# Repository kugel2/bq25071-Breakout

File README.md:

# bq25071-Breakout
Breakoutboard 20x20mm for bq25071 LiFePo4 linear charger ic.

**_Warning_: this board is not finished**

**_Warning_: this board is not tested**

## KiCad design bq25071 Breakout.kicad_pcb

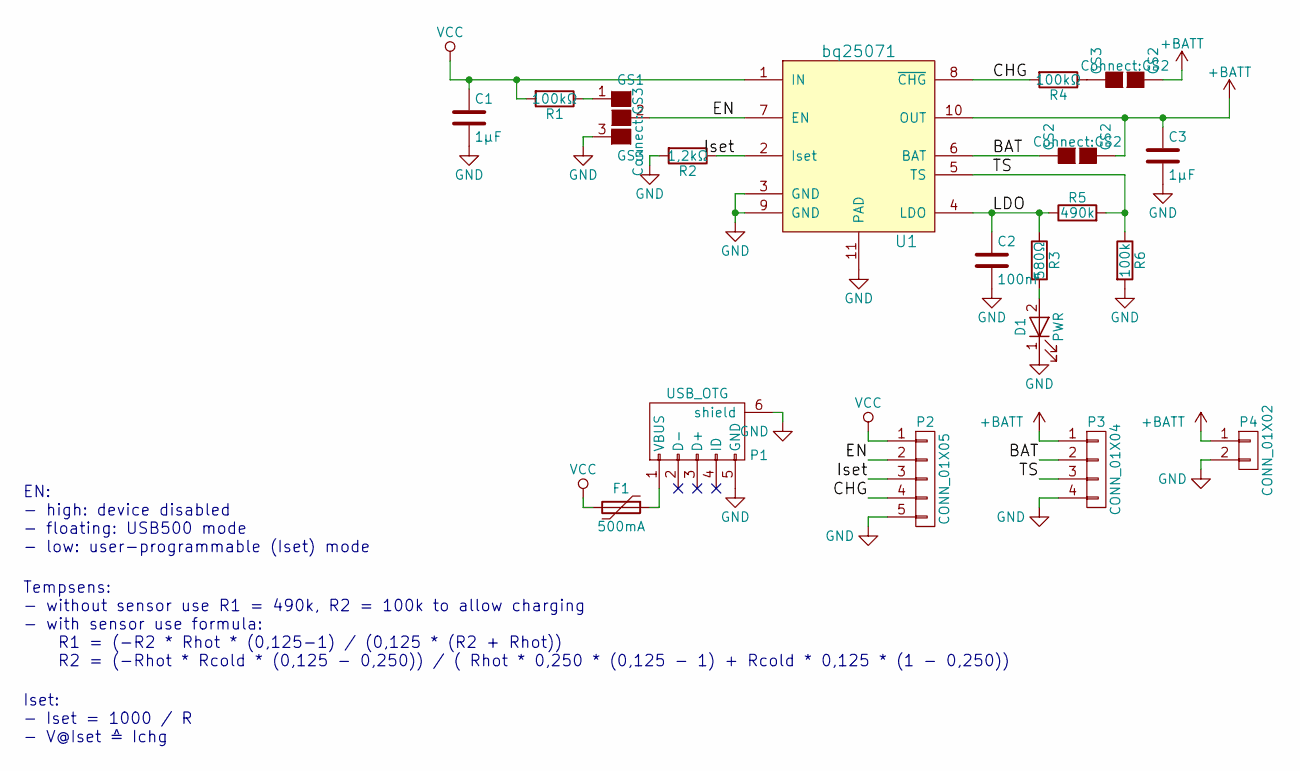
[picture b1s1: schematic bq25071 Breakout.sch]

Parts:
C1, C3: 1µF; C_1206
C2: 100nF; C_0805
D1: PWR; LED_0805
F1: 500mA; R_1206
GS1: GS3
GS2, GS3: GS2
P1: USB_OTG; USB_MICRO_B_MOLEX
P2: CONN_01X05; Pin_Header_Straight_1x05_Pitch2.54mm
P3: CONN_01X04; Pin_Header_Straight_1x04_Pitch2.54mm
P4: CONN_01X02; JST_XH_B02B-XH-A_02x2.50mm_Straight
R1, R4: 100kΩ; R_0805
R2: 1,2kΩ; R_0805
R3: 580Ω; R_0805
R5: 490k; R_0805
R6: 100k; R_0805
U1: bq25071; DFN-10-1EP_2x3mm_Pitch0.5mm

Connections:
+BATT: C3.1, GS2.2 (G2), GS3.2 (G2), P3.1, P4.1, U1.10 (OUT)
/BAT: GS2.1 (G1), P3.2, U1.6 (BAT)
/CHG: P2.4, R4.2, U1.8 (~CHG)
/EN: GS1.2 (G2), P2.2, U1.7 (EN)
/Iset: P2.3, R2.1, U1.2 (Iset)
/LDO: C2.1, R3.1, R5.1, U1.4 (LDO)
/TS: P3.3, R5.2, R6.1, U1.5 (TS)
GND: C1.2, C2.2, C3.2, D1.1 (K), GS1.3 (G3), P1.5 (GND), P1.6 (shield), P2.5, P3.4, P4.2, R2.2, R6.2, U1.3 (GND), U1.9 (GND), U1.11 (PAD)
unnamed: D1.2 (A), R3.2
unnamed: F1.1, P1.1 (VBUS)
unnamed: GS1.1 (G1), R1.1
unnamed: GS3.1 (G1), R4.1
VCC: C1.1, F1.2, P2.1, R1.2, U1.1 (IN)

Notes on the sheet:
Tempsens: - without sensor use R1 = 490k, R2 = 100k to allow charging - with sensor use formula: R1 = (-R2 * Rhot * (0,125-1) / (0,125 * (R2 + Rhot)) R2 = (-Rhot * Rcold * (0,125 - 0,250)) / ( Rhot * 0,250 * (0,125 - 1) + Rcold * 0,125 * (1 - 0,250))
EN: - high: device disabled - floating: USB500 mode - low: user-programmable (Iset) mode
Iset: - Iset = 1000 / R - V@Iset ≙ Ichg

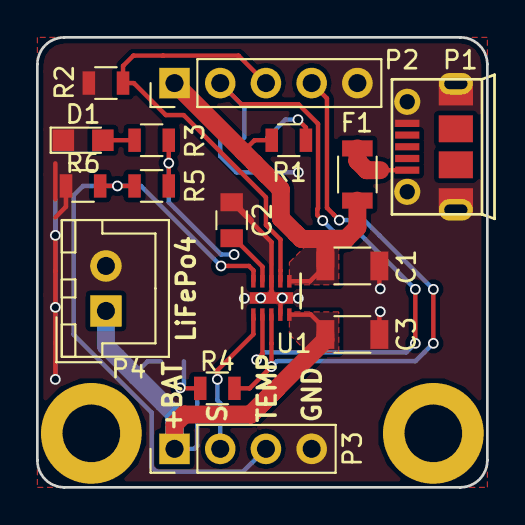
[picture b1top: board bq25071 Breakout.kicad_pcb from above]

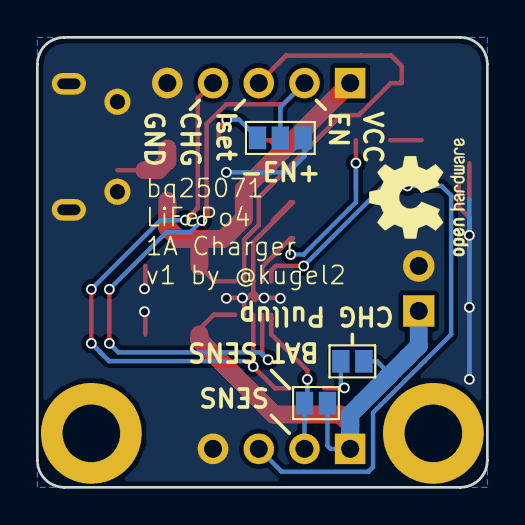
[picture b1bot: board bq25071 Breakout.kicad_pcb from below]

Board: 2 copper layers, 25.0 x 25.0 mm, 19 parts (3 on the bottom side), 13 nets.

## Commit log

2017-03-30 pcb layout
2017-03-30 addendum for #d8ad44f
2017-04-08 better component placement
2017-04-08 silkscreen
2017-04-08 add 3d renderings from kicad
2017-04-08 change battery connector to jst xh (seems to be standard for rc lipos)
2017-04-09 add gerber and pdf
2017-04-09 update pictures
2017-04-09 addendum
